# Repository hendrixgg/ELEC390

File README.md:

# ELEC390
Queen's University 3rd year design project course on a small autonomous vehicle. 

Website for contest information: https://queensuca.sharepoint.com/teams/CCT-938446/SitePages/LearningTeamHome.aspx

# Tasks
- [x] prioritize tasks: everything with names on it are due by feb 11 ✅ 2025-01-28
- [x] write about ethics issue with road rule R4, conversation with Gregory Kelly @Hendrix ✅ 2025-02-08
    - My question: Will we get an "R4: Stay On the Road" infraction if we drive off the road to avoid another vehicle driving head-on to us?
    - Gregory's response: That's a really interesting question. Got a good bit of discussion going in the teaching team's meeting. We aren't really even certain how it would be handled under real-life road laws (it appears it would be initially assessed, but a lot would come down to specifics and lawyers). For the time being, we've decided that R4 would still apply. However, we are considering mechanisms that would appropriately reward teams who achieve this type of capability. Regardless of how the rules evolve, this decision would make an excellent ethics consideration in your logbook and reports.
- [ ] finish setting up PiCarX as described on the SharePoint @Luke
- [ ] set up programming/testing environment on the PiCarX so that we can rapidly test all features @Jacob
    - [ ] figure out software development environment (combining Python and C)
    - [ ] make PiCarX remote controllable or at least programmable (figure out the drive control interface)
    - [ ] make PiCarX able to sense data from all sensors simultaneously
    - [ ] make PiCarX able to record sensor data (ideally so that we can live stream sensor data to a laptop, perhaps at least the head camera feed)
    - [ ] set up high-level software interface between sensors and drive controls and API calls so that we can incrementally add in each new feature as it is developed
- [ ] make PiCarX able to run software on both Raspberry Pi and Coral TPU
    - [ ] figure out how to run stuff on the Coral TPU
- [ ] determine strategy for different detection of objects/patterns 
    - [ ] road signs (stop, no entry, yield, one way) @Hendrix
        - [ ] upload dataset of readsigns 📅 2025-03-07
    - [ ] road markings (road boundary, road center line, intersection stop line, cross walk, one way arrow) @Jacob
    - [ ] road obstacles (vehicles, duck pedestrians, other objects) @Hendrix
        - [ ] take photos of specialty duck we got 📅 2025-03-07
- [x] represent the map of Quackston in software that aligns with the VPFS @Hendrix ✅ 2025-02-09
    - [x] see website: ✅ 2025-02-09
        - https://queensuca.sharepoint.com/teams/CCT-938446/SitePages/The-Town.aspx
        - https://queensuca.sharepoint.com/teams/CCT-938446/SitePages/GPS-and-Fare-System.aspx
    - [x] see [[ELEC390/ELEC390/Design/mapping/README|README]] for details
- [ ] VPFS Setup @Matt
    - [ ] make PiCarX able to send API calls to VPFS and store results
    - [ ] perhaps use flask, find some other library
- [ ] setup basic vehicle controls @Jacob
    - [ ] acceleration motors
    - [ ] steering servo
- [ ] setup vehicle signaling @Luke
    - [ ] put break and turn signal lights on PiCarX
    - [ ] make break light system work
        - [ ] specify what states of the vehicle will trigger brake lights
    - [ ] make turn signal light system work
        - [ ] specify blinking rate and high-level software control interface
- [ ] miscellaneous vehicle controls @Luke
    - [ ] head camera servos
    - [ ] duck lift servos
- [ ] Test physical capabilities of drive controls
    - [ ] we could get some rubber matt to test the car on for feb 8
    - [ ] turn radius at different speeds and road surfaces (feb 11)
    - [ ] top speed on different road surfaces (feb 11)
    - [ ] minimum braking distance at different speeds and road surfaces from the point in time when braking is initiated in software
        - [ ] figure out how we are going to measure this (perhaps using the grayscale line detector?)
- [ ] break down more tasks here
    - [ ] route planning (optimal sequence of road and intersections between two destinations on the map)
    - [ ] path planning (specific path on the road to be followed by drive controls)
    - [ ] ride selection
    - [ ] position generation
    - [ ] represent the reward system / road rules in software
    - [ ] be able to infer vehicle position based on sensor data
    - [ ] be able to infer other object positions base on sensor data
    - [ ] implement autonomous driving capabilities

# Complete
- [x] Project Proposal Report 📅 2025-01-26 ✅ 2025-01-26
    - [x] Write Sections📅 2025-01-25 
        - [x] Executive Summary @Hendrix ✅ 2025-01-26
        - [x] Project Management @Hendrix ✅ 2025-01-26
        - [x] Finish up data sources (where to get data) @Hendrix ✅ 2025-01-26
        - [x] Conclusions @Matt
    - [x] Review and edit sections 🛫 2025-01-25 📅 2025-01-26 ✅ 2025-01-26
        - [x] Jacob ✅ 2025-01-26
        - [x] Hendrix ✅ 2025-01-26
        - [x] Luke ✅ 2025-01-26
        - [x] Matt ✅ 2025-01-26
    - [x] ensure consistent formatting
        - [x] remove our names in headings 
        - [x] paragraph spacing and indenting (vspace vs. newline vs. `\\` vs. `\\\\`?) (decided on indenting all but the first paragraph in a section)
        - [x] technologies and tools table formatting
            - [x] Hendrix needs to update python libraries
        - [x] references 
            - [x] Jacob
            - [x] Hendrix
            - [x] Luke
            - [x] Matt
    - [x] submit [on OnQ](https://onq.queensu.ca/d2l/lms/dropbox/user/folder_submit_files.d2l?db=409840&grpid=979636&isprv=0&bp=0&ou=938446) ✅ 2025-01-26
- [x] Design Headlight Board for taxi
- [x] Create Lift for duck passengers

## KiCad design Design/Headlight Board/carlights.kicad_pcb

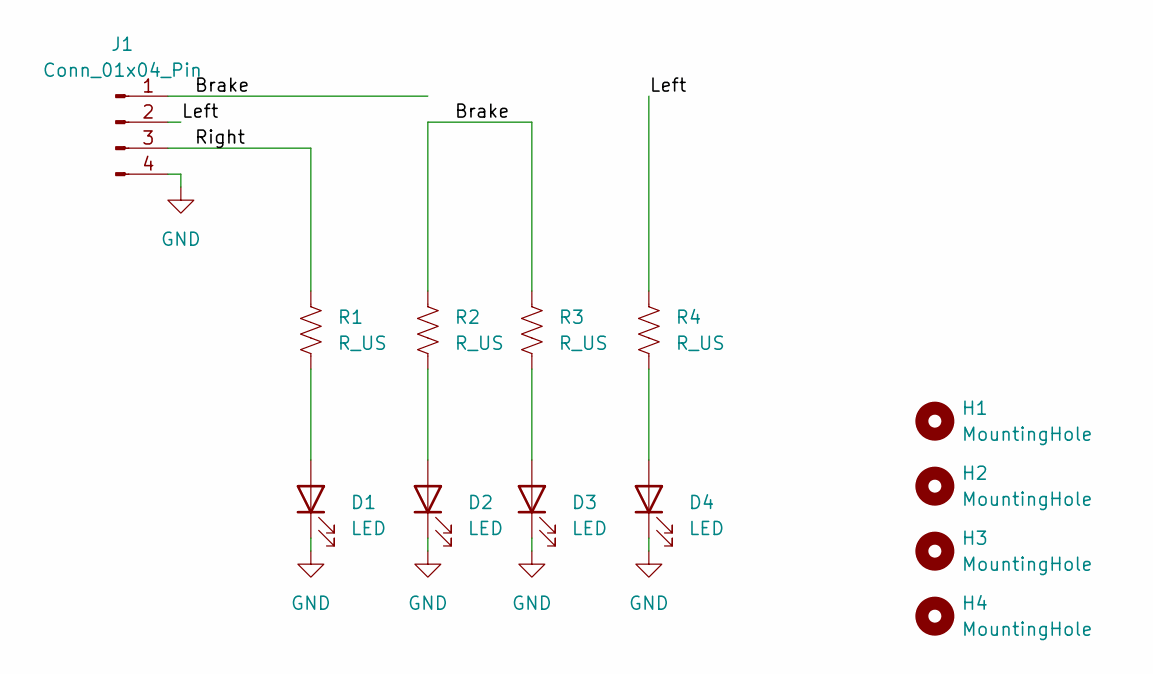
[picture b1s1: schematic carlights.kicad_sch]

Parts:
D1, D2, D3, D4: LED; LED_D5.0mm_Clear
H1, H2, H3, H4: MountingHole; MountingHole_2.5mm
J1: Conn_01x04_Pin; PinHeader_1x04_P2.54mm_Vertical
R1, R2, R3, R4: R_US; R_Axial_DIN0414_L11.9mm_D4.5mm_P15.24mm_Horizontal

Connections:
/Brake: J1.1, R2.1, R3.1
/Left: J1.2, R4.1
/Right: J1.3, R1.1
GND: D1.1 (K), D2.1 (K), D3.1 (K), D4.1 (K), J1.4
unnamed: D1.2 (A), R1.2
unnamed: D2.2 (A), R2.2
unnamed: D3.2 (A), R3.2
unnamed: D4.2 (A), R4.2

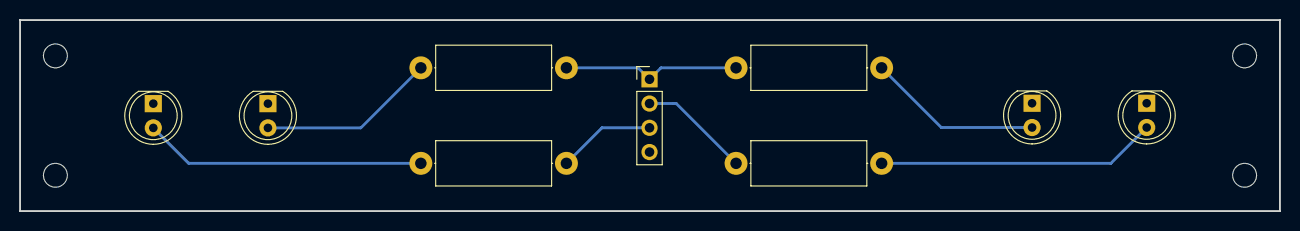
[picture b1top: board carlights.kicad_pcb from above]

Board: 2 copper layers, 131.9 x 20.0 mm, 13 parts (0 on the bottom side), 8 nets.

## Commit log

2025-01-21 canvas
2025-01-21 ultrasonic
2025-01-21 deliverable instructions added.
2025-01-21 organize
2025-01-24 added to-do list to readme
2025-01-24 added task
2025-01-25 added map svg images
2025-01-25 updated to do list
2025-01-26 Added the Headlight KiCad project
2025-01-26 work on project work breakdown
2025-01-27 checked off some todo items
2025-01-27 clarified todo item
2025-01-27 Project Proposal Report Submitted
2025-01-27 added a bunch of Tasks
2025-01-28 delegated todo items from third lab session
2025-01-29 added item to write about in logbook
2025-02-01 picode
2025-02-01 install pi stuff
2025-02-01 driving
2025-02-04 updated hendrix's todos in readme
2025-02-07 got the raspberry pi's MAC Address
2025-02-09 specified map and routing model for the car, next step is to decide whether to implement in C or python
2025-02-09 clarified some pseudocode, and seems like we'll probably implement the routing algorithm in python
2025-02-11 started python data modelling
2025-02-23 fix submodules
2025-02-24 reverse engineering ip
2025-02-24 re adc + mtr
2025-02-24 removed pydantic as a dependency
2025-02-24 clarified map routing data model
2025-02-24 trip route data validation works
2025-02-25 copied map coordinates into csv files and moved svg files around
2025-02-25 more work on routing
2025-02-25 update oral assessment instructions
2025-02-26 update .gitignore to ignore pychace
2025-02-26 fixed __pycache__ gitignore
2025-02-26 basic floyd warshall router works
2025-02-26 corrected import
2025-02-26 updated docstring
2025-02-26 next step for mapping noted
2025-02-26 create prj
2025-02-27 drive works
2025-02-27 drive works no sudo
2025-02-27 basic map routing complete. see README.md for possible enhancements.
2025-02-27 updated comment on sorting of map edges in csv file
2025-02-27 made roads visible again in svg
2025-02-27 removed stop signs from road markings map svg
2025-02-27 wip turn
2025-02-27 turning
2025-02-27 turning works
2025-02-27 wip cam
2025-02-27 wip lift
2025-02-27 lift kinda works
2025-02-27 wip dist
2025-02-28 all works
2025-02-28 migration start
2025-02-28 pix node
2025-02-28 testing
2025-02-28 controller
2025-02-28 stuff
2025-03-05 diff turn
2025-03-05 launch
2025-03-05 launch joy
2025-03-05 launch stuffs
2025-03-05 tooning
2025-03-05 start roadline
2025-03-07 build script
2025-03-07 ignore comp cmnds
2025-03-07 ignore clang cache
2025-03-07 building
2025-03-07 launch cvtest
2025-03-09 mapping functionality documentation written
2025-03-23 roadline_tracking
2025-03-23 imagres
2025-03-23 fix pi build
2025-03-23 states change
2025-03-24 jetson launch
2025-03-24 added updated waypoints for intersection stop points
2025-03-24 move to vision
2025-03-24 jetson
2025-03-24 directions can now be generated from trip routing
2025-03-25 vision duck avoid
2025-03-25 testing turning complete
2025-03-25 full test working
2025-04-02 Final report instructions revised
2025-04-07 routing and system build pipeline
2025-04-07 another diagram for trip routing and distance estimating
2025-04-07 included obsidian canvas file for map routing build pipeline
2025-04-07 Final report added
